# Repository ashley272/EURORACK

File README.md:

# ST MODULAR
_EURORACK DIY_

This repository was made to provide you with the neccessary information to source your parts and find their place on the PCB. There won´t be full build documentations available at any time in the future. 

If you have questions before or while building please join the [ST Modular Builders Group](https://www.facebook.com/groups/stmodular/) on Facebook. There you will also find additional information about the builds in the "lessions" section.

I also recommend to fully read the "Eurorack Soldering Guide" available above. It includes a step-by-step description how I solder DIY projects, a list of recommended soldering tools and some links that might be useful when jumping into Eurorack DIY.

If you got ST Modular PCBs you will need to solder 0603 packaged components. The PCBs are not necessarily designed to be builder friendly as there are very tiny components included (e.g. SOD-523 diodes). Therefore the modules are recommended to be soldered by experienced builders only. Successful construction, safe powering and necessary calibration of the module is purely your responsibility. You are solely responsible for ensuring the finished module will not damage other equipment that you connect it to. Damage to other equipment is your responsibility. I am not responsible if you injure yourself or others, or damage any of your property or others property during the construction or use of PCBs provided.

I do not offer or perform repairs of any type.

For more information about the functionality of the modules please visit [www.st-modular.com](http://www.st-modular.com).

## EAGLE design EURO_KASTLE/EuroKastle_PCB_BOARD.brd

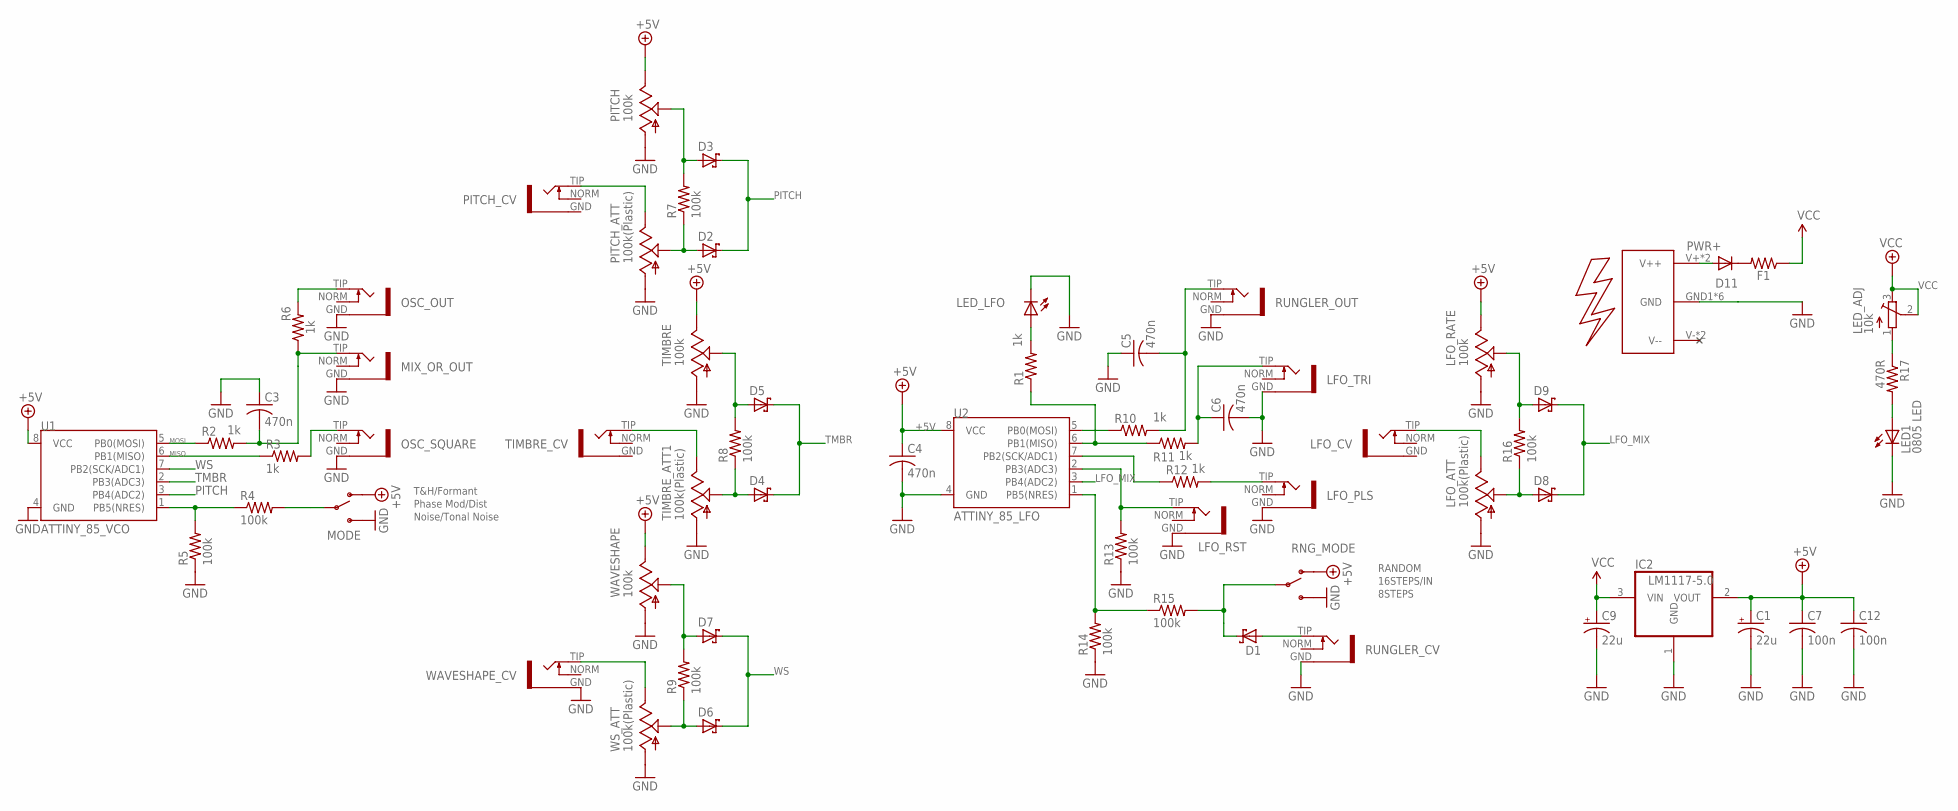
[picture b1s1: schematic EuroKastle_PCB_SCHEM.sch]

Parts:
C1, C9: 22u; E2,5-6
C3, C4, C5, C6: 470n; C0603
C7, C12: 100n; C0603
D1, D2, D3, D4, D5, D6, D7, D8, D9: 610-CMDZ5L1; SOD323(F)
D11: 1N5819HW; SOD123
F1: 100Ohms; R0603
IC2: LM1117-5.0; SOT223
LED1: 0805 LED; CHIP-LED0805
LED_ADJ: 10k; TC33X
LED_LFO: LED3MM
LFO_ATT: 100k(Plastic); 9MM_SNAP-IN_POT
LFO_CV: INSTRUO_S_JACK_SMALL2
LFO_PLS: INSTRUO_S_JACK_SMALL2
LFO_RATE: 100k; 9MM_SNAP-IN_POT
LFO_RST: INSTRUO_S_JACK_SMALL2
LFO_TRI: INSTRUO_S_JACK_SMALL2
MIX_OR_OUT: INSTRUO_S_JACK_SMALL2
MODE: SPDT_ON_OFF_ON_SUBMINI; SUBMINI_TOGGLE
OSC_OUT: INSTRUO_S_JACK_SMALL2
OSC_SQUARE: INSTRUO_S_JACK_SMALL2
PITCH: 100k; 9MM_SNAP-IN_POT
PITCH_ATT: 100k(Plastic); 9MM_SNAP-IN_POT
PITCH_CV: INSTRUO_S_JACK_SMALL2
POWER: EURO_POWER2
R1, R2, R3, R6, R10, R11, R12: 1k; R0603
R4, R5, R7, R8, R9, R13, R14, R15, R16: 100k; R0603
R17: 470R; R0603
RNG_MODE: SPDT_ON_OFF_ON_SUBMINI; SUBMINI_TOGGLE
RUNGLER_CV: INSTRUO_S_JACK_SMALL2
RUNGLER_OUT: INSTRUO_S_JACK_SMALL2
TIMBRE: 100k; 9MM_SNAP-IN_POT
TIMBRE_ATT1: 100k(Plastic); 9MM_SNAP-IN_POT
TIMBRE_CV: INSTRUO_S_JACK_SMALL2
U1: ATTINY_85_VCO; DIP08_MCU
U2: ATTINY_85_LFO; DIP08_MCU
WAVESHAPE: 100k; 9MM_SNAP-IN_POT
WAVESHAPE_CV: INSTRUO_S_JACK_SMALL2
WS_ATT: 100k(Plastic); 9MM_SNAP-IN_POT

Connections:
+5V: C1.+, C4.1, C7.1, C12.1, IC2.2 (VOUT), LFO_RATE.3 (E), MODE.1 (O), PITCH.3 (E), RNG_MODE.1 (O), TIMBRE.3 (E), U1.8 (VCC), U2.8 (VCC), WAVESHAPE.3 (E)
GND: C1.-, C3.1, C4.2, C5.1, C6.2, C7.2, C9.-, C12.2, IC2.1 (GND), LED1.C, LED_LFO.K (C), LFO_ATT.1 (A), LFO_PLS.GND, LFO_RATE.1 (A), LFO_RST.GND, LFO_TRI.GND, MIX_OR_OUT.GND, MODE.3 (S), OSC_OUT.GND, OSC_SQUARE.GND, PITCH.1 (A), PITCH_ATT.1 (A), POWER.GND1 (GND), POWER.GND2 (GND), POWER.GND3 (GND), POWER.GND4 (GND), POWER.GND5 (GND), POWER.GND6 (GND), R5.1, R13.1, R14.1, RNG_MODE.3 (S), RUNGLER_CV.GND, RUNGLER_OUT.GND, TIMBRE.1 (A), TIMBRE_ATT1.1 (A), U1.4 (GND), U2.4 (GND), WAVESHAPE.1 (A), WAVESHAPE_CV.GND, WS_ATT.1 (A)
LFO_MIX: D8.1 (K), D9.1 (K), U2.3 (PB4(ADC2))
MISO: R3.1, U1.6 (PB1(MISO))
MOSI: R2.1, U1.5 (PB0(MOSI))
unnamed: C3.2, MIX_OR_OUT.TIP, R2.2, R6.1
unnamed: R4.1, R5.2, U1.1 (PB5(NRES))
unnamed: OSC_SQUARE.TIP, R3.2
unnamed: MODE.COM (COMMON), R4.2
unnamed: OSC_OUT.TIP, R6.2
unnamed: PITCH_ATT.3 (E), PITCH_CV.TIP
unnamed: D2.2 (A), PITCH_ATT.2 (S), R7.1
unnamed: TIMBRE_ATT1.3 (E), TIMBRE_CV.TIP
unnamed: D3.2 (A), PITCH.2 (S), R7.2
unnamed: D4.2 (A), R8.1, TIMBRE_ATT1.2 (S)
unnamed: D5.2 (A), R8.2, TIMBRE.2 (S)
unnamed: D6.2 (A), R9.1, WS_ATT.2 (S)
unnamed: WAVESHAPE_CV.TIP, WS_ATT.3 (E)
unnamed: D7.2 (A), R9.2, WAVESHAPE.2 (S)
unnamed: R10.1, U2.5 (PB0(MOSI))
unnamed: C5.2, R10.2, RUNGLER_OUT.TIP
unnamed: R1.1, R11.1, U2.6 (PB1(MISO))
unnamed: C6.1, LFO_TRI.TIP, R11.2
unnamed: LFO_RST.TIP, R13.2, U2.2 (PB3(ADC3))
unnamed: R12.1, U2.7 (PB2(SCK/ADC1))
unnamed: LFO_PLS.TIP, R12.2
unnamed: R14.2, R15.1, U2.1 (PB5(NRES))
unnamed: LFO_ATT.3 (E), LFO_CV.TIP
unnamed: D1.2 (A), RUNGLER_CV.TIP
unnamed: D8.2 (A), LFO_ATT.2 (S), R16.1
unnamed: D9.2 (A), LFO_RATE.2 (S), R16.2
unnamed: D1.1 (K), R15.2, RNG_MODE.COM (COMMON)
unnamed: LED_LFO.A, R1.2
unnamed: LED1.A, R17.2
unnamed: LED_ADJ.1 (A), R17.1
unnamed: D11.C, F1.2
PITCH: D2.1 (K), D3.1 (K), U1.3 (PB4(ADC2))
PWR+: D11.A, POWER.V+ (V++), POWER.V++
TMBR: D4.1 (K), D5.1 (K), U1.2 (PB3(ADC3))
VCC: C9.+, F1.1, IC2.3 (VIN), LED_ADJ.2 (S), LED_ADJ.3 (E)
WS: D6.1 (K), D7.1 (K), U1.7 (PB2(SCK/ADC1))

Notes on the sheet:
Phase Mod/Dist
T&H/Formant
Noise/Tonal Noise
16STEPS/IN
RANDOM
8STEPS

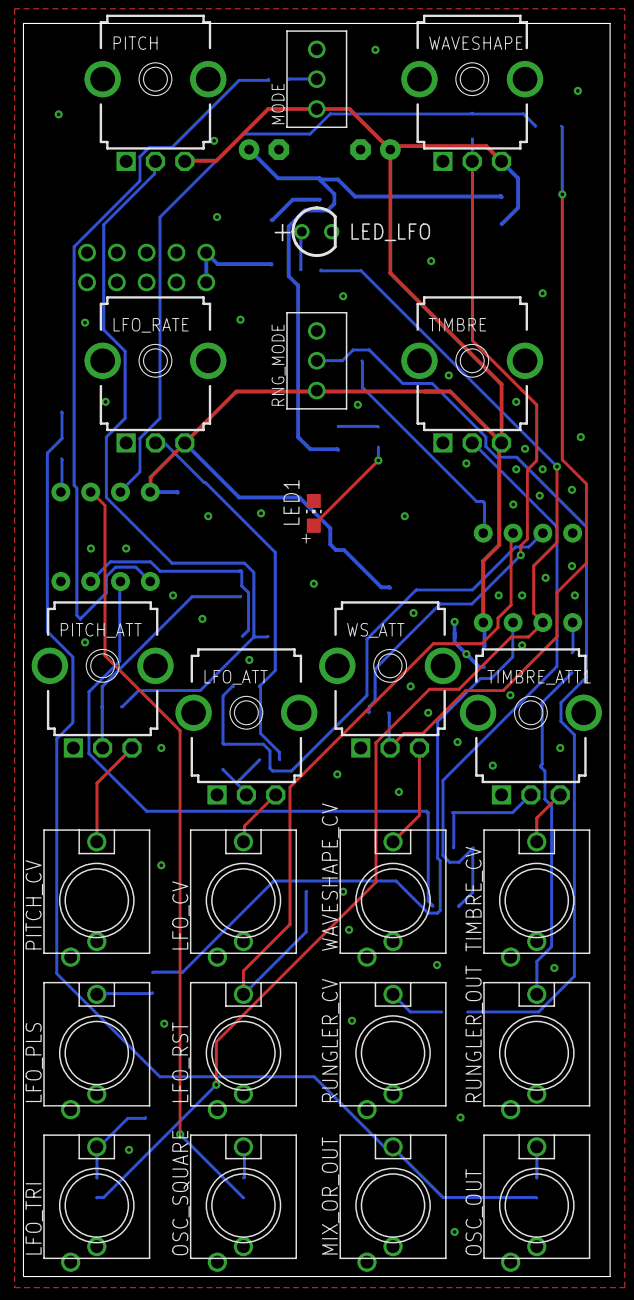
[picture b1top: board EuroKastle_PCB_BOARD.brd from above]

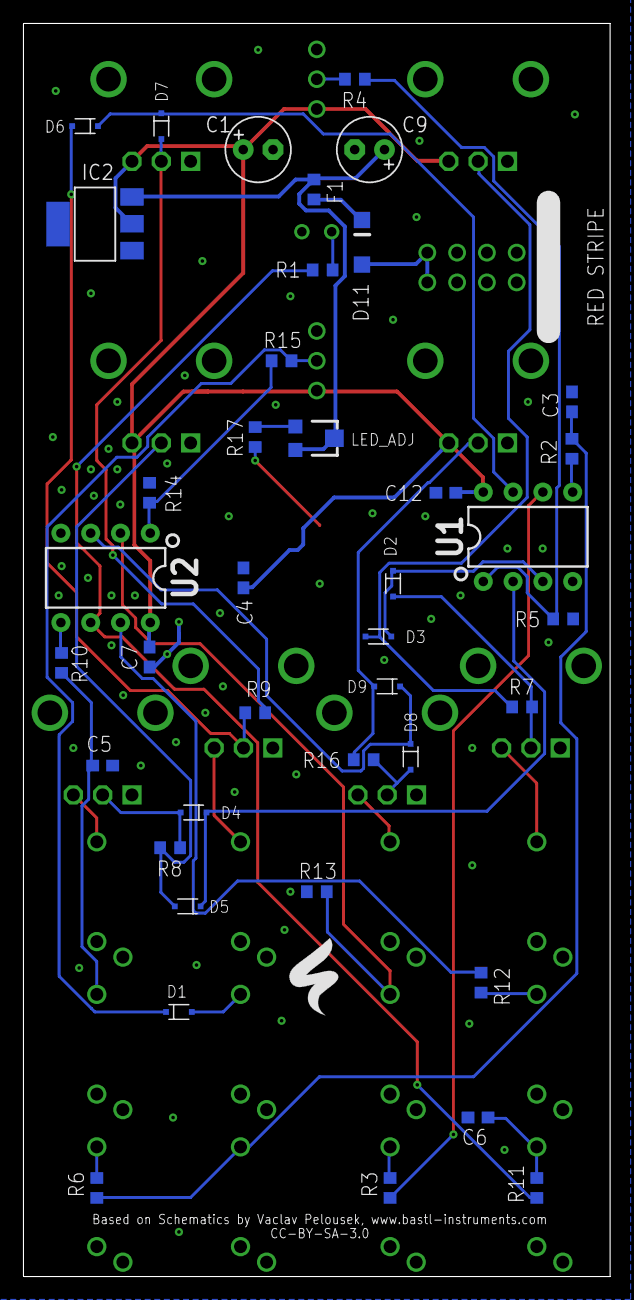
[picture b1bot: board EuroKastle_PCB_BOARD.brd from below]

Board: 2 copper layers, 50.0 x 106.8 mm, 65 parts (41 on the bottom side), 41 nets.

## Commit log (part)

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2018-10-31 Create index
2019-02-07 Create review
2019-02-07 Create Available soon!
2019-02-07 Rename Available soon! to 1_Available soon!
2019-02-07 Rename 1_Available soon! to 1_AVAILABLE SOON!
2019-02-07 Create 1_AVAILABLE SOON!
2019-03-24 Create init
2019-03-24 Update and rename init to readme
2019-04-10 Rename readme to Changelog_V2
2019-04-10 Update Changelog_V2
2019-04-13 Create iBOM
2019-04-13 Create readmne
2019-05-04 Create V2
2019-06-13 Create Links
2019-09-14 Create DRILL_FILES
2020-03-21 Create Reqadme
2020-04-24 Create Readame

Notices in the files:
EURO_KASTLE/EuroKastle_PCB_BOARD.brd:
CC-BY-SA-3.0
parts and their libraries:
SparkFun-Retired: Licensing: Creative Commons ShareAlike 4.0 International - https://creativecommons.org/licenses/by-sa/4.0
